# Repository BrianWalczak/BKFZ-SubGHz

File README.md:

<h1 align="center">BKFZ SubGHz</h1>
<p align="center">A robust program for your ESP32 to capture and replay SubGHz frequencies, inspired by the Flipper Zero and written in Arduino + React Native.</p>

> [!WARNING]
> **Heads up! Major changes have been made since the previous release. If you encounter any issues, please report them <a href='https://github.com/brianwalczak/BKFZ-SubGHz/issues'>here</a>.**

## Features
- (📻) **Record RAW** - Capture and save SubGHz radio frequencies with a configurable RSSI threshold (saved as `.sub`).
- (📡) **Replay/Emulate RAW** - Easily transmit SubGHz radio frequencies from file (no SD card required).
- (🔍) **Frequency Analyzer** - Scan and analyze nearby devices across multiple frequencies (300-928 MHz).
- (⚙️) **Custom Presets** - Support for various digital modulations and frequency bands with customizable presets.
- (🛜) **Wi-Fi/Bluetooth Connectivity** - Support for both Bluetooth and Wi-Fi based connectivity (web server).
    - (📱) **Mobile App** - Cross-platform mobile application for Bluetooth, powered by React Native (iOS + Android).
    - (🌐) **Web App** -  WebSocket-powered web app for Wi-Fi connectivity, works on any device with a browser.
- (🐬) **Flipper Zero Support** - Built with Flipper Zero native support, allowing you to record and play `.sub` files.
- (🔋) **Portable Design** - Custom PCB design for battery-powered operation with a compact design.
- (👤) **Open Source** Open-source under Apache 2.0 license - contribute or view it anytime.

## Requirements
To start, you'll need (by minimum) an [**ESP32**](https://s.click.aliexpress.com/e/_DCh9q31) [$2.97] of your choice and a [**CC1101 RF Transceiver**](https://s.click.aliexpress.com/e/_DlNeVmT) [$2.01]. You can purchase both of these parts in the links provided.

> [!CAUTION]
> **When choosing a CC1101 module, make sure to select the operating frequency that is most commonly used in your region. The** `433 MHz` **frequency band is generally most common, but this may vary based on the device you're attempting to emulate.<br><br>Your module can use either a [wire antenna](https://s.click.aliexpress.com/e/_DlNeVmT) or an [SMA antenna](https://s.click.aliexpress.com/e/_Dn4dKAr) — both options are compatible.**

If you're looking to build a fully-fledged BKFZ SubGHz device, you'll want to purchase these additional components (about **~$13.03**):
- [2000mAh Lithium Battery](https://s.click.aliexpress.com/e/_DnKGR3V): **$6.03** on AliExpress (**ensure your ESP32 includes a built-in voltage regulator, or attach one separately**)
- [TP4056 Module (5pk)](https://s.click.aliexpress.com/e/_Dd8V8J1): **$1.36** on AliExpress
- [Latching Buttons (10pk)](https://s.click.aliexpress.com/e/_DkSsHEL): **$1.13** on AliExpress 
- [JST 2mm Connectors (10pk)](https://s.click.aliexpress.com/e/_DCTEiy7): **$1.01** on AliExpress 
- [Custom PCB Print](https://github.com/brianwalczak/BKFZ-SubGHz/tree/main/KiCad_PCB#bkfz-subghz---kicad-pcb): **~$3.50** on JLCPCB (w/ shipping)
<br>

The custom PCB design, as found [here](https://github.com/brianwalczak/BKFZ-SubGHz/tree/main/KiCad_PCB#bkfz-subghz---kicad-pcb), is specifically designed to work with the 433 MHz module(s) linked above.

## Getting Started
To flash the BKFZ SubGHz program on your ESP32, you'll need to connect the CC1101 module first. By default, the following pinout is used:
| ESP32 | CC1101 |
|----------|----------|
| GND | GND |
| 3.3V | VCC |
| G5 | CSN |
| G13 | MOSI |
| G19 | MISO |
| G14 | SCK |
| G16 | GDO0 |
| G18 | GDO2 |

If you'd like to use a different pinout, you can configure the pins in the `headers/config.h` configuration file.

Additionally, **you'll need to decide which connection mode you'd like to use**. By default, your BKFZ SubGHz device will use Bluetooth Low Energy for communication with the **mobile app**. If you'd like to use Wi-Fi connectivity (or your device does not support the mobile app), you should modify the `CONNECTION_MODE` definition to `CONNECTION_MODE_WIFI` in the configuration file.

**Note:** If possible, Bluetooth connectivity is highly recommended as it's more reliable on mobile devices.

To install the BKFZ SubGHz firmware, you'll need to open this repository in Arduino IDE in the `Arduino/` folder.

---

### Wi-Fi Connection

If you've selected Wi-Fi as the connection mode, you'll need to download and install the [LittleFS Upload](https://github.com/earlephilhower/arduino-littlefs-upload) plugin (you can find instructions on installation in the repository). This plugin is crucial to serve essential files through the web server (CSS, fonts, icons, etc).

Next, you should upload the `data/` files through LittleFS (`Ctrl` + `Shift` + `P`, then `Upload LittleFS to Pico/ESP8266/ESP32`). **Make sure your Serial Monitor is closed during the uploading process.**

---

Lastly, click the `Upload` icon in the Arduino IDE to flash the code on your ESP32. All done!

## Usage
Once you've completed the firmware installation, it's time to access the interface! There are multiple ways to do this, depending on the connection mode you've selected.

### Bluetooth Connection

> [!WARNING]
> Currently, the BKFZ SubGHz mobile app must be sideloaded on your device while I work to publish it on the Google Play Store. Due to App Store restrictions, iOS devices will **always** require manual sideloading through Xcode. Please follow the instructions below to continue.

To access the user interface on a Bluetooth connection, you'll need to download the official **BKFZ SubGHz** app for iPhone or Android.

To compile the application manually, start by installing the required dependencies in this repository:
```bash
git clone https://github.com/brianwalczak/BKFZ-SubGHz.git
cd BKFZ-SubGHz/Application
npm install
```

Next, follow the instructions below based on your device's operating system:

#### iOS Devices
In order to sideload the application to your iPhone, you'll need to install Xcode [here](https://apps.apple.com/us/app/xcode/id497799835) on a Mac and login to an Apple ID (free or paid).

Next, you'll need to download Xcode Command Line Tools for compatibility with Expo:
```bash
xcode-select --install
```

Follow the instructions on your Mac to finish installation, then plug in your iOS device. To begin building the application, run this command:
```bash
npx expo run:ios --device --configuration Release
```

This process may take a few minutes, and the application will be installed to your device once complete. You may need to trust the developer on your iPhone to launch the application (`Settings > General > VPN & Device Management`, under `Developer App`).

#### Android Devices
There are two different ways you can install the BKFZ SubGHz app on your Android device.

- Visit the releases page [here](https://github.com/brianwalczak/BKFZ-SubGHz/releases) to download and install the latest pre-compiled APK.
- Plug in your Android device, then run `npx expo run:android --variant release` (you will need to install [Android SDK Platform-Tools](https://developer.android.com/tools/releases/platform-tools)).

### Wi-Fi Connection

1. Open the Wi-Fi settings on your mobile device and connect to the `BKFZ SubGHz` Wi-Fi network (remember, you can configure the SSID and password in the configuration file).
2. Open your browser and navigate to `192.168.4.1` to view the interface.
3. Click the Connect button to establish a connection with the BKFZ SubGHz device (via WebSockets).

If the page is not found, check the `Gateway` IP address of the Wi-Fi network and navigate to the IP address.

**Tip:** If you'd like to add the user interface as a web app to your home screen, you can click `Share > Add to Home Screen` in Safari for iOS, or the 3 dots in Chrome for Android.

## Credits/Authors
This project was made possible by utilizing the following dependencies:
- [`ELECHOUSE_CC1101_SRC_DRV`](https://www.arduino.cc/reference/en/libraries/smartrc-cc1101-driver-lib/) | A library for controlling the CC1101 module, which is commonly used for wireless communication in Arduino projects.
- [`ESPAsyncWebServer`](https://www.arduino.cc/reference/en/libraries/espasyncwebserver/) | A library that enables the creation of web servers on the ESP32 and ESP8266.
- [`React Native`](https://reactnative.dev/) | A popular open-source framework for building native mobile apps using React.
- [`Expo`](https://expo.dev/) | A full-stack React Native framework that makes development, testing, and deployment of apps much easier.
- [`ESP32 Core Libraries`](https://github.com/espressif/arduino-esp32/tree/master/libraries) | A collection of libraries pre-installed on the ESP32 (including Wi-Fi, SPI, LittleFS, Preferences, and much more).
- [`Flipper Zero`](https://github.com/flipperdevices/flipperzero-firmware) | This project couldn't be made possible without the extensive documentation and awesome team over at Flipper Zero ♥

These are just a couple honorable mentions; view the `package.json` and Arduino code for more details!

## FAQ

### Does this project allow me to emulate devices with iButton, NFC/RFID, or Infrared technology?
No, the BKFZ SubGHz can **not** emulate any of these types of devices, unlike the Flipper Zero. This project is specifically focused on replicating the SubGHz functionality of the Flipper Zero. However, it is theoretically possible to achieve this with an ESP32 and the appropriate module (though it's unlikely to happen).

### Do I need a paid Apple Developer account to install the app?
Nope! If you have access to Xcode, you can use a free Apple ID to sideload the app. However, you will need to re-install the application every **7 days** due to iOS restrictions, so it's recommended that you use Wi-Fi connectivity instead. Sorry!

### Do I need to have an internet connection?
You don't need internet access to use the BKFZ SubGHz, however you will need to connect to its Wi-Fi access point if you're using Wi-Fi Connection Mode (learn more [here](#wi-fi-connection-1)).

### Who is maintaining this project behind the scenes?
At the moment, this project is solely developed and maintained by me (thanks to the amazing resources [here](#creditsauthors)). That said, I highly encourage you to contribute to the project by submitting a pull request! It would be greatly appreciated.

### I found a bug or would like to submit feedback.
That's great to hear! You can submit any feedback, or any bugs that you find, on the <a href='https://github.com/brianwalczak/BKFZ-SubGHz/issues'>issues page</a>. I check these very frequently, and I highly encourage you to find bugs.

### I love this project! How can I support its maintenance?
I'm glad to hear that you find this project useful! If you'd like to support this project and its development, you can send me a tip <a href='https://ko-fi.com/brianwalczak'>here</a> 😁

<br>
  <p align="center">Made with ♡ by <a href="https://brian.re/">Briann</a></p>

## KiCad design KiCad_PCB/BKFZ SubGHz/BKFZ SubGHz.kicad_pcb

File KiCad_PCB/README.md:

# BKFZ SubGHz - KiCad PCB
A custom-designed printed circuit board designed for connecting a [Wemos D1 Mini](https://s.click.aliexpress.com/e/_DCh9q31) (ESP32), a [CC1101](https://s.click.aliexpress.com/e/_DlNeVmT) module, and a [TP4056](https://s.click.aliexpress.com/e/_Dd8V8J1) battery module (optional). This PCB was designed for the BKFZ SubGHz as an easy way to connect the components.

This PCB was designed in KiCad (you can import it with `File > Open Project` and exported as a ready-to-print Gerber file. I printed this PCB for about **$3.50** (quanity of 5) on [JLCPCB](https://jlcpcb.com/) (not sponsored).

### Assembly
> **If you'd like to see detailed photos of each step in the assembly process, you can check them out [here](https://github.com/BrianWalczak/BKFZ-SubGHz/tree/main/Other/Assembly%20Photos).**

To assemble the BKFZ SubGHz device, I began by soldering female headers onto the PCB. This allows for easy attachment and removal of the ESP32 and CC1101 (if any changes are necessary). I started by soldering female headers on the underside of the PCB, and then soldered male headers to the ESP32, pointing upward, as shown below:

<br><br>

Once this was completed, I moved on to the TP4056 module and the JST connector. I soldered the positive and negative wires from the battery to the appropriate terminals on the TP4056. Next, I soldered two smaller wires to the `OUT-` and `OUT+` terminals for the power output:

<br><br>

To secure the latching power button, I used double-sided tape and attached it on the side the female headers for convenience (had to get creative with it 😅). I soldered the positive wire from the TP4056 to one end of the button, and then added a red wire to the other end. The negative wire from the TP4056 was soldered directly to the negative SMD pad on the PCB, while the positive wire (from the other end of the button) was soldered to the positive SMD pad:

<br><br>

> [!TIP]
> **This button design allows the device to be powered on and off, helping to preserve battery life and prevent interference with other devices.**

Finally, I connected the battery to the JST connector, and that's it! We've successfully built our own BKFZ SubGHz device.

### Photos
This project utilized the Wemos D1 Mini symbol and footprint by [@r0oland](https://github.com/r0oland/ESP32_mini_KiCad_Library), as well as the TP4056 battery module footprint by [@ccadic](https://github.com/ccadic/TP4056-18650). The CC1101 symbol and footprint was designed by me, as I was unable to find it online anywhere.

#### Schematic

#### PCB Design

<br><br>

**If you'd like to see detailed photos of each step in the assembly process, you can check them out [here](https://github.com/BrianWalczak/BKFZ-SubGHz/tree/main/Other/Assembly%20Photos).**

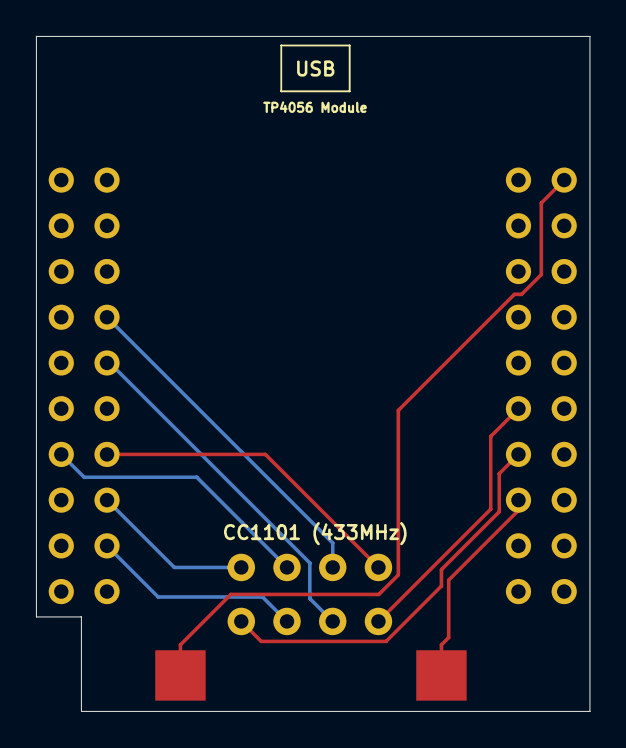
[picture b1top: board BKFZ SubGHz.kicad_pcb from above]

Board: 2 copper layers, 30.8 x 37.5 mm, 3 parts (0 on the bottom side), 6 nets.

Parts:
CC1101_433MHz1: CC1101_SubGHz
ESP32_D1_Mini1: ESP32_Mini
TP4056_18650: TP4056_18650

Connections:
unnamed: CC1101_433MHz1.5 (GND), ESP32_D1_Mini1.33 (GND)
unnamed: CC1101_433MHz1.6 (MOSI), ESP32_D1_Mini1.18 (IO_13/TCK)
unnamed: CC1101_433MHz1.2 (SCK), ESP32_D1_Mini1.13 (IO_14/TMS)
unnamed: CC1101_433MHz1.1 (VCC), ESP32_D1_Mini1.16 (3V3)
unnamed: ESP32_D1_Mini1.35 (VCC_(USB)), TP4056_18650.3 (OUT+)
unnamed: ESP32_D1_Mini1.22 (GND), TP4056_18650.4 (OUT-)

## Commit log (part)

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2024-09-21 Insert documentation
    This commit includes simple documentation to setting up your own BKFZ SubGHz device. This also includes the Apache License for this project.
2024-09-21 Create PCB directory
    This commit includes the instructions for printing and connecting the custom PCB, specially designed for the BKFZ SubGHz!
2024-09-21 🎉 v1.0.0 | BKFZ SubGHz
    This commit includes version 1.0.0 of BKFZ SubGHz! This version is currently in its beta state, and bugs are to be expected.
2024-10-20 Insert compiled gerber file
2024-10-20 Insert KiCad symbol + footprint library, and schematic + PCB design
2024-10-20 Update assembly instructions w/ photos
2024-10-20 Upload assembly photos
2024-10-20 🎉 v2.0.0 | BKFZ SubGHz
    This commit includes version 2.0.0 of BKFZ SubGHz! This version is currently in its beta state, and bugs are to be expected.
2025-10-25 Cleanup code, add sample recording improvements, fix analyzer
2025-10-26 Add no RSSI threshold
2025-10-26 Update presets data to replicate Flipper Zero
2025-10-26 Update graphing logic client-side
2025-10-26 Build app initial commit
2025-10-26 Change app folder location
2025-10-26 Add bluetooth off component
2025-10-26 Add bluetooth error component
2025-10-26 Create dynamic bluetooth warning page
2025-10-27 Create dynamic warning page
2025-10-27 Add permissions check, scan for bluetooth devices
2025-10-27 Display bluetooth devices, fix devices logic
2025-10-27 Add device connection logic
2025-10-27 Add connection timeout 10s
2025-10-27 Only allow BKFZ devices w/ name
2025-10-27 Move permissions to global context, poll permissions
2025-10-27 Fix permission polling logic
2025-10-27 Move bluetooth logic to global context for background listeners
2025-10-27 Move device connection logic to global context
2025-10-27 Use device connection logic from global context
2025-10-27 Remove page switch logic
2025-10-27 Add onConnectPeripheral event
2025-10-27 No need to update btConnected w/ event listeners already registered
2025-10-27 Switch pages on connect/disconnect
2025-10-27 Check for existing connections, add name filtering
2025-10-27 Fix stale variables, cleanup calllbacks
2025-10-27 Fix more stale variables for event listeners
2025-10-27 Gray out button while connecting device
2025-10-27 Create basic home page (might change later)
2025-10-27 Move GlobalContext to providers/
2025-10-28 Move header definitions, create interfaces, re-structure code
2025-10-28 Add better explanation of config files
2025-10-28 Move saveSettings to user_settings.cpp
2025-10-28 Move preferences instance to user_settings.cpp
2025-10-28 Remove handlers, just add the logic right then and there!
    Just noticed it'd be easier if I include flushSamples and playSignal thru interface.h so I can include the logic directly in the WiFi interface.
2025-10-28 Create globals header w/ variables
2025-10-28 Migrate to LittleFS for better compatibility
2025-10-29 Add bluetooth notification logic
2025-10-29 Add utility to send data via bluetooth
2025-10-29 Add end marker for writing data, parse end marker for receiving data
2025-10-29 Create BLE interface, add marker logic, fix includes for interfaces.
2025-10-30 Use larger MTU for faster data transmission
2025-10-30 Fix MTU negotiation for iOS devices
    Devices running iOS < 10 will request an MTU size of 158. Newer devices running iOS 10 will request an MTU size of 185.
    https://stackoverflow.com/questions/41977767/negotiate-ble-mtu-on-ios/42336001
2025-10-30 Add bluetooth data events to register across pages
2025-10-30 Create record page w/ file saving implementation
2025-10-30 Update event registering logic for BLE
2025-10-30 Get settings on new established bluetooth connection
2025-10-30 Show actual settings on load
2025-10-31 Small changes to record.tsx
2025-10-31 Fix frequency analyzer to check for no values
2025-10-31 Create frequency analyzer page!
2025-10-31 Create changelog and update warning
2025-11-01 Add app demo in changelog.
2025-11-01 Add web demo in changelog.
    This is an old video, but I think it explains pretty well!
2025-11-04 Add settings saving logic, create updateSettings function
2025-11-04 Remove unnecessary success confirmation
    We'll just assume it was successful, cause otherwise the device would be disconnected (which would just prompt re-connection in the app).
2025-11-04 Update detect_rssi locally when analyzer RSSI changed
2025-11-04 Remove logging (we're done debugging!)
2025-11-04 Check for first time user, display welcome page (under construction)
2025-11-04 Remove faulty dependency for iOS
2025-11-04 Fix iOS app permissions
2025-11-04 Fix permissions in app.json
2025-11-04 Truncate device name / ID if too large
2025-11-05 Check for permissions on iOS
2025-11-05 Add deprecated bluetooth permission for iOS to be safe
2025-11-05 Small changes to connection page style, added retry Bluetooth scanning
2025-11-05 Fix bluetooth scanning logic and adjust for iOS compatibility
2025-11-05 Remove logging during development
2025-11-05 Lower Bluetooth scan interval, clear devices on disconnect
2025-11-05 Clear list of devices on new scan
2025-11-05 Create universal back button, update to useRouter from useNavigation
2025-11-05 Add universal back button to all pages, use SafeAreaView.
2025-11-06 Begin building read page, create file reading util, fix typos
2025-11-06 Add percentage calculation for playing files
2025-11-06 Update play page to show LIVE progress percentage
2025-11-06 Use smooth animation for playing files
2025-11-06 Add bluetooth compatibility for react-native-permissions (iOS)
2025-11-06 Move toast messages to _layout and make global.
2025-11-06 Rename index.tsx to connect.tsx, rename welcome.tsx to index.tsx.
2025-11-06 Show welcome page by default, also fixing the page animation direction!
2025-11-06 Create custom icon, favicon, and splash for mobile app.
2025-11-06 Fix package versions, wait for settings before page load
2025-11-06 Update app demo recording
2025-11-10 Update font to Roboto, looks better!
2025-11-11 Begin working on data protocol, create basic structure
    Warning, this is currently still very experimental and is a breaking change! I'm not yet done working on this, and I'll be working on full implementation later this week.
    This is my first time doing something like this, so it'll take some time!
2025-11-12 Remove settings status and options inject, store options directly in js
2025-11-12 Add reader for byte data in React app, fix settings bug!
2025-11-12 Fix critical bug for samples + graphing
    As I mentioned, first time doing this stuff and I guess I didn't do my research lol... memcpy won't work in our case. Iterating over the data is much safer!
2025-11-12 Move SUB file creation from device to application (client-side).
2025-11-13 Add byte data payload builder in React App.
2025-11-13 Use same variable for buffer storage in GlobalContext.tsx (reset on new connection)
2025-11-13 Add reader for byte data in Arduino code (finally remove JSON)!
    Still working on implementation for settings updates. I've merged together analyzer's detect_rssi setting with the standard settings SET command.
2025-11-14 Update settings values from data, fix settings bug!
2025-11-14 Remove unused imports, fix dependency arrays
    `npx expo lint`
2025-11-14 Fix Bluetooth scanning with new refactored API
    https://github.com/innoveit/react-native-ble-manager/commit/4e579fe214f850b9eb4e85ade404e4de6b83743a#diff-a2a171449d862fe29692ce031981047d7ab755ae7f84c707aef80701b3ea0c80
2025-11-14 Fix bugs and type safety for settings, add null checks
2025-11-15 Remove unused dependencies
2025-11-17 Minor improvements to sample/graph arrays (minimize memory usage), fix comments
2025-11-18 Migrate to expo-document-picker for web compatibility
2025-11-18 Update readFileContent to handle both native and web
2025-11-18 Create simple WebSocket implementation of GlobalContext for web platform
2025-11-18 Separate GlobalContext.tsx to web and native.
2025-11-18 Create connect page for web platform
2025-11-18 Specify specific imports for vector-icons to save storage
2025-11-18 Remove Ionicons and bluetooth from MaterialIcons, use Feather instead
2025-11-18 Create brotli compression helper for web.
2025-11-19 Replace brotli compression with gzip for HTTP support
    Although brotli is much better, sadly this has to be done for support on Chromium and Firefox :(
2025-11-19 Remove all old assets/data for LittleFS
2025-11-19 Begin rebuilding wifi_interface.cpp, add static file serving
2025-11-19 Fix back navigation to support web
    If a user refreshes the page, the router history is lost, therefore we should check for the window history instead if it exists. If not, hide the back arrow.
2025-11-19 Update React function name for /connect
2025-11-19 Remove connect page for web, create custom index.tsx for web w/ connectivity logic
2025-11-19 Add support for Press Start 2P font on web (remove spaces)
2025-11-19 Add command events for Websocket
2025-11-19 Minor bug fixes for data send/receive with Websockets
2025-11-20 Add web compatibility for record.tsx, phase out ArduinoJson, other minor changes
2025-11-20 Initial build of React web app w/ gzip compression
2025-11-20 Add unexpected disconnect warning, create connection timeout for Websockets
2025-11-20 Improve troubleshooting println's to `Serial`
2025-11-20 Update message popup logic, include animation fade in/out
2025-11-20 Set Bluetooth as default connection mode (recommended)
2025-11-20 Fix critical bug for RSSI threshold setting
2025-11-21 Update README instructions, add new demo videos to CHANGELOG
2026-01-04 add app mockups
2026-01-11 new domain
2026-02-12 add mockups to readme
